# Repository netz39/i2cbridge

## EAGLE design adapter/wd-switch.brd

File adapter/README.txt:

== I³C-Adapter aus der Ampel ==
adapter.brd
adapter.sch
i2c_adapter_trove.gcode
i2c_adapter_trove.scad

== I³C-Adapter mit WatchDog-Switch aus der Rollladen-Steuerung ==
wd-switch.brd
wd-switch.sch

== alter I³C-Adapter aus der Rollladen-Steuerung ==
wd-adapter.brd
wd-adapter.sch

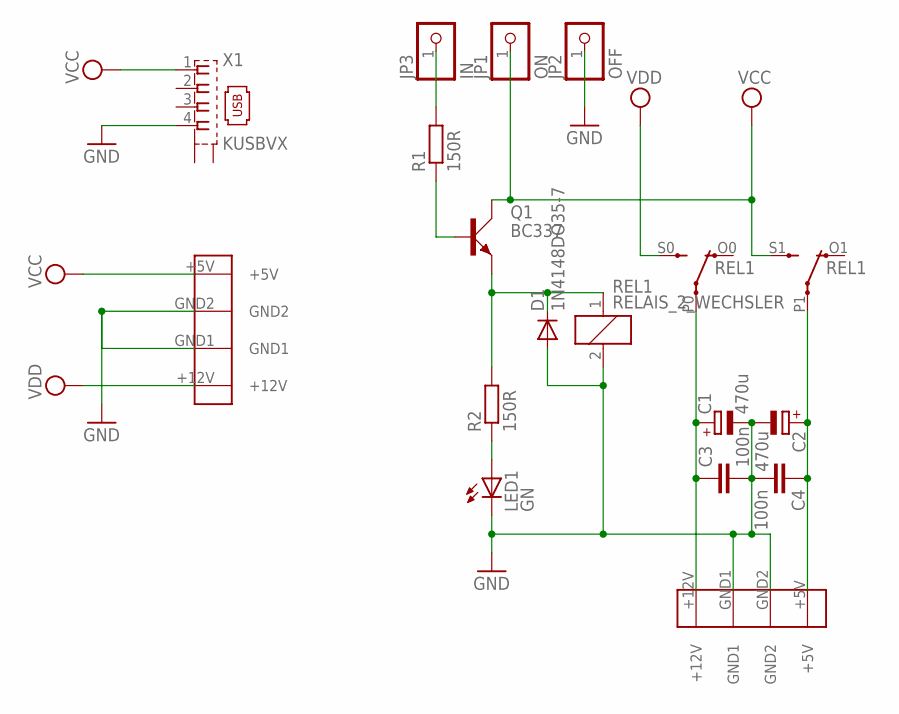
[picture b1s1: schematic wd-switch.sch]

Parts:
C1, C2: 470u; E3,5-8
C3, C4: 100n; C025-024X044
D1: 1N4148DO35-7; DO35-7
IN: PSW_5
JP1: ON; 1X01
JP2: OFF; 1X01
JP3: IN; 1X01
LED1: GN; LED5MM
OUT: PSW_5
Q1: BC337; SOT54A
R1: 150R; 0207/2V
R2: 150R; 0207/7
REL1: RELAIS_2_WECHSLER; RELAIS_DIL_M4
X1: KUSBVX

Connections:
GND: C1.-, C2.-, C3.2, C4.2, D1.A, IN.GND1, IN.GND2, JP2.1, LED1.K (C), OUT.GND1, OUT.GND2, REL1.2, X1.4
unnamed: JP3.1, R1.2
unnamed: C1.+, C3.1, OUT.+12V, REL1.P0
unnamed: Q1.B, R1.1
unnamed: C2.+, C4.1, OUT.+5V, REL1.P1
unnamed: LED1.A, R2.1
unnamed: D1.C, Q1.E, R2.2, REL1.1
VCC: IN.+5V, JP1.1, Q1.C, REL1.S1 (S), X1.1
VDD: IN.+12V, REL1.S0 (S)

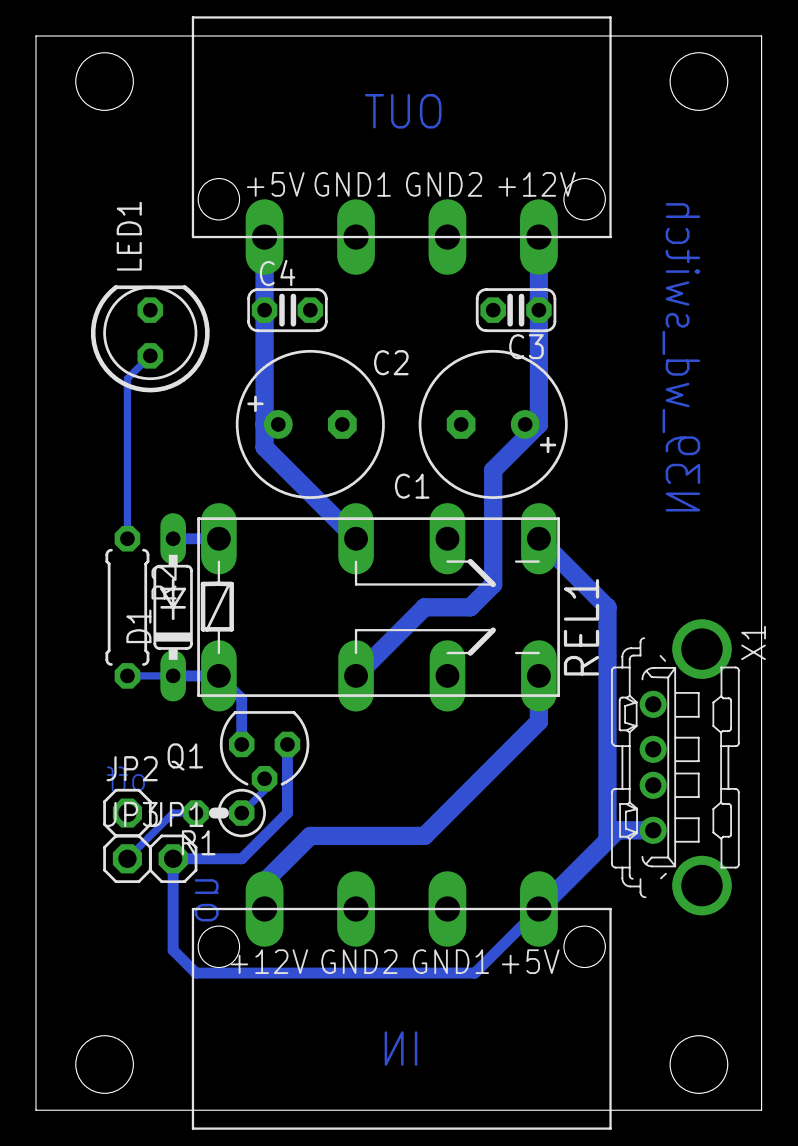
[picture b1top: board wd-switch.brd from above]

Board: 2 copper layers, 40.3 x 59.7 mm, 16 parts (0 on the bottom side), 9 nets.

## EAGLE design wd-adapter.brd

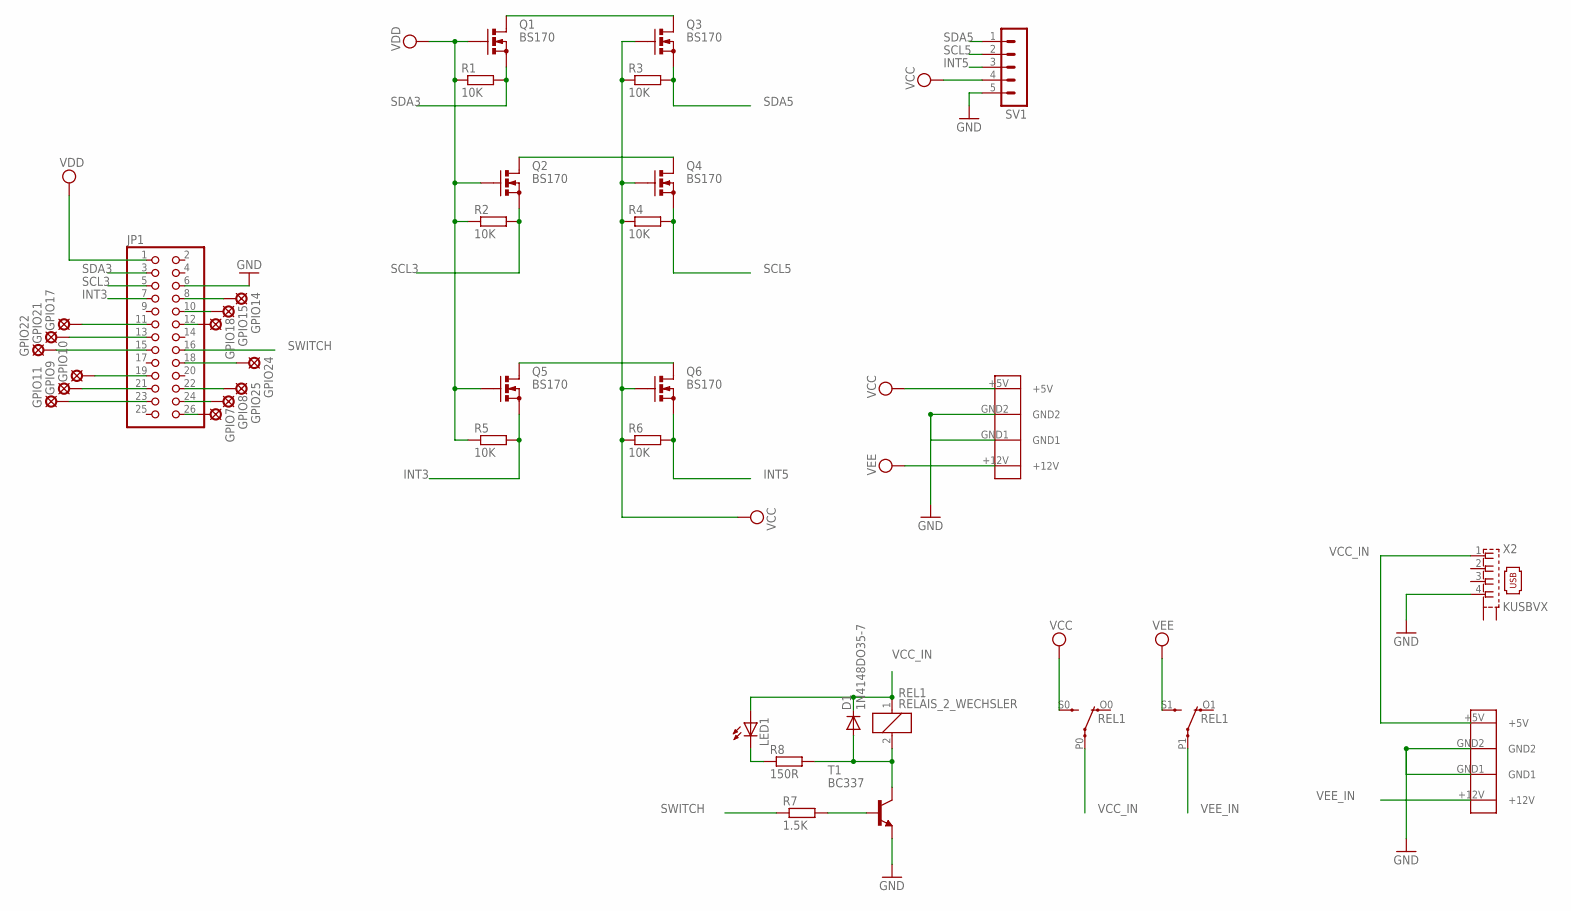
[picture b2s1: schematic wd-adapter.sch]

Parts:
D1: 1N4148DO35-7; DO35-7
GPIO7, GPIO8, GPIO9, GPIO10, GPIO11, GPIO14, GPIO15, GPIO18, GPIO21, GPIO22, GPIO24, GPIO25: LSP10
GPIO17: GPIO17; LSP10
JP1: PINHD-2X13; 2X13
LED1: LED3MM
Q1, Q2, Q3, Q4, Q5, Q6: BS170; SOT54E
R1, R2, R3, R4, R5, R6: 10K; 0207/2V
R7: 1.5K; 0207/7
R8: 150R; 0207/2V
REL1: RELAIS_2_WECHSLER; RELAIS_DIL_M4
SV1: MA05-1
T1: BC337; TO92
U$1, U$3: PSW_5
X2: KUSBVX

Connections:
GND: JP1.6, SV1.5, T1.1 (E), U$1.GND1, U$1.GND2, U$3.GND1, U$3.GND2, X2.4
INT3: JP1.7, Q5.S, R5.2
INT5: Q6.S, R6.2, SV1.3
unnamed: GPIO17.MP, JP1.11
unnamed: GPIO21.MP, JP1.13
unnamed: GPIO22.MP, JP1.15
unnamed: GPIO10.MP, JP1.19
unnamed: GPIO9.MP, JP1.21
unnamed: GPIO11.MP, JP1.23
unnamed: GPIO14.MP, JP1.8
unnamed: GPIO15.MP, JP1.10
unnamed: GPIO18.MP, JP1.12
unnamed: LED1.K (C), R8.1
unnamed: GPIO24.MP, JP1.18
unnamed: GPIO25.MP, JP1.22
unnamed: GPIO8.MP, JP1.24
unnamed: GPIO7.MP, JP1.26
unnamed: Q1.D, Q3.D
unnamed: Q2.D, Q4.D
unnamed: Q5.D, Q6.D
unnamed: D1.A, R8.2, REL1.2, T1.3 (C)
unnamed: R7.2, T1.2 (B)
SCL3: JP1.5, Q2.S, R2.2
SCL5: Q4.S, R4.2, SV1.2
SDA3: JP1.3, Q1.S, R1.2
SDA5: Q3.S, R3.2, SV1.1
SWITCH: JP1.16, R7.1
VCC: Q3.G, Q4.G, Q6.G, R3.1, R4.1, R6.1, REL1.S0 (S), SV1.4, U$1.+5V
VCC_IN: D1.C, LED1.A, REL1.1, REL1.P0, U$3.+5V, X2.1
VDD: JP1.1, Q1.G, Q2.G, Q5.G, R1.1, R2.1, R5.1
VEE: REL1.S1 (S), U$1.+12V
VEE_IN: REL1.P1, U$3.+12V

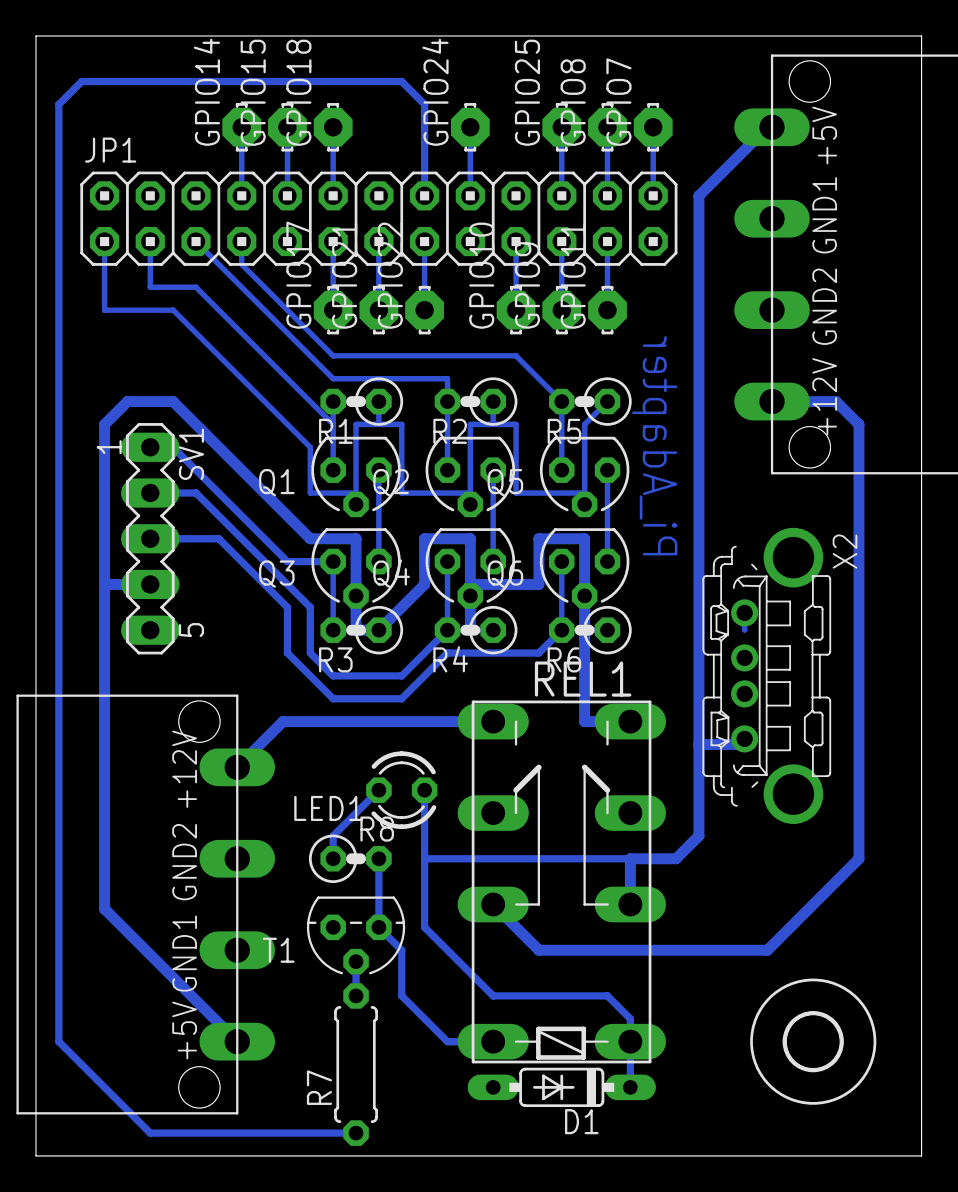
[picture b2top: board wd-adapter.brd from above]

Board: 2 copper layers, 49.2 x 62.2 mm, 37 parts (0 on the bottom side), 32 nets.

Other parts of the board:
U$2: 3,0

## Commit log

2013-04-20 I2C-Adapter
2013-04-20 letzte Anpassungen zum Ätzen
2013-04-22 Redesign (INT-Leitung und breitere Leitung für Spannungsversorgung)
2013-04-24 Adapter: stecker angepasst Controller: board redesign
2013-05-05 trove für den i2c-adapter
2013-05-05 Gehäusedesign v2
2013-05-05 Kleine Anpassungen im SCAD-Script
2013-05-05 trove v3
2013-05-06 anpassung an i2c-board
2013-05-06 kräftigeres Gehäuse und Snapper
2013-10-24 pending changes
2013-11-23 Switch für den Watchdog
2013-11-24 * Bohrlöcher xD * kleine Verbesserungen im Platinenlayout
2013-11-24 Pinheaders für statische Schalterstellung
2013-11-25 USB-Stromversorgung
2013-12-01 Werte für die Kondensatoren angegeben
2013-12-19 Korrigiertes Design
2013-12-21 WD-Switch jetzt mit Relais
2013-12-22 kleine Layoutanpassung, um GND-Durchlass zu verbreitern
2013-12-22 Korrigiertes M4-Relais eingesetzt
2014-01-02 Integrierter I³C-Pegeladapter mit WatchDog-Switch
2014-01-03 Zustands-LED eingebaut
2014-01-03 Übrige Leiterbahn entfernt
2014-01-05 Fehlendes Routing fehlt m(
2014-01-30 add raspberry/i2cbridge, untested
2014-01-31 i2cbridge: fix Makefile
2014-01-31 i2cbridge: fix sprintf path length
2014-01-31 i2cbridge: fix sun_family and addrsize
2014-01-31 i2cbridge: fix i2c poll bug
2014-01-31 i2cbridge: add info output
2014-01-31 i2cbridge: remove superfluous buf variable
2014-01-31 i2cbridge: add reuse_sockaddr
2014-01-31 i2cbridge: fix i2c handling
2014-01-31 i2cbridge: add simple client
2014-01-31 i2cbridge: remove client binary, add to .gitignore
2014-02-01 i2cbridge: add unix client
2014-02-15 i2cbridge: autotoolize - add manpages
2014-02-15 i2cbridge: remove ntoh/hton for data, this is end device specific and therefore irrelevant
2014-02-15 i2cbridge: rename clients
2014-02-15 i2cbridge: add autogen.sh
2014-02-16 i2cbridge/shuttercontrol: fix missing socket ipc suffix
2014-02-16 i2cbridge: fix pid to lockfile
2014-02-16 i2cbridge: add verbose option
2014-02-16 i2cbridge: add options explicit enabling of inet or unix service
2014-02-16 i2cbridge: get the client return right - add verbose option for clients, default print only data - update manpages, include error codes
2014-02-16 i2cbridge: dont link clients against wiringPi
2014-02-16 i2cbridge: fix permissions - fix working dir permissions - add -m option to set unix socket permissions
2014-02-16 i2cbridge: add warning cflags, fix warnings & missing licenses
2014-02-23 Added the debian packaging data (not necessarily in an optimal/final form)
2014-02-26 moved adapter board files to subdirectory
2014-02-26 remove unneeded files
2014-02-26 ReadMe für Ampel-Adapter
2014-02-26 gcode-File des i2c-adapters
2014-02-26 moved adapter files from SpaceNotification to adapter sub-directory
2014-02-26 ReadMe-File ergänzt
